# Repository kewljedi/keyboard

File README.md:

# keyboard

The purpose of this project is to make they keyboard that I want to use. It isn't a full keyboard instead it is a programable set of hot keys. 

Now of course the fact that I want these hot keys to be able to control things like tmux, vscode, and the like, doesn't make this keyboard nearly geeky enough, so it needs rgb leds, underglow, and a host of other cool things that the [Quantum Mechanical Keyboard Firmware](http://qmk.fm) affords those that use it.

This is a learning experience, the idea is to learn about electronics pcb design, and refresh my electronics knowledge. As a learning aid I started with [ruiqimao's keyboard pcb guide](https://github.com/ruiqimao/keyboard-pcb-guide).

## SIGHT

### underglow
To be able to pull of the awesome underglow effect we will be using the WS2812 RGB Addressable LED. I picked this because it is the same as the LEDs that are supported by the RBG Matrix. 

Parts
* [WS2812](https://www.sparkfun.com/products/16346)

### rgb matrix 
Of course each key needs an RGB Led of it's own. To accomplish this WS2812 comes to the rescue.

Parts
* [WS2812](https://www.sparkfun.com/products/16346)

### rotary encoders
A little bit of spin can go along way, if it is just to change the volume, or scrub through audio or video every good purpose built keyboard should have one rotary encoder at least, this keyboard will have RGB enabled ones. To do this the RGB Led inside the rotary encoder will be connected to a WS2811 Chip that will make the LED in the rotary encoder exactly like the NeoPixels used for the rest of the lighting. Don't forget the rotary encoder also contains a button.

Parts
* [Rotary Encoder](https://www.sparkfun.com/products/15141)
* [Clear Knob](https://www.sparkfun.com/products/10597)
* [LED Driver Chip WS2811](https://www.adafruit.com/product/1378)

## HEARING

### keys
[Gateron MX SMD Browns](https://www.amazon.com/Switches-Underglow-Compatible-Mechanical-Transparent/dp/B07K829KDW?th=1)

### speakers
Yes this board have two separate voices! It will play 8-bit tunes.

## FEELING

### keys
Cherry MX ... (still no color choice)

### keycaps 
I haven't decided but, I was thinking.

Parts 
* [Clear Keycaps](https://www.sparkfun.com/products/15306)

### haptic feedback
Now the feedback of the keys alone just wont cut it for this keyboard, it must be able to let us know when we have enters certain modes or functions.

Parts
* [DRV2605L](https://www.ti.com/product/DRV2605L?HQS=TI-null-null-digikeymode-df-pf-null-wwe&DCM=yes&distId=10)
* [Linear resonant actuators](https://www.digikey.com/product-detail/en/jinlong-machinery-electronics-inc/G0832013D/1670-1078-ND/9974290)

### case
So why stop learning wth just electronics and learning about the firmware? I think building the case will be just as much fun. I am thinking maybe wood, and epoxy resin (clear). One thing I want to keep in mind for the design of the case is wrist support.

### wires
No tug. Hopefully the only time you need to attach a USB-C cable to the keyboard is to charge it (though it should work wth one connected to you computer). This means that we have to have Bluetooth and Batteries.

Parts
* [Battery](https://www.sparkfun.com/products/12895)
* [Battery Holder](https://www.sparkfun.com/products/14963)
* [Battery Management]()
* [Bluetooth Module](https://www.adafruit.com/product/2633)

Insanity Parts
* [Wireless Power Receiver](https://www.sparkfun.com/products/15934)
* [Wireless Power Transmitter](https://www.sparkfun.com/products/15935)

## TASTE
By this point lets all agree ths keyboard sounds awesome enough to lick...

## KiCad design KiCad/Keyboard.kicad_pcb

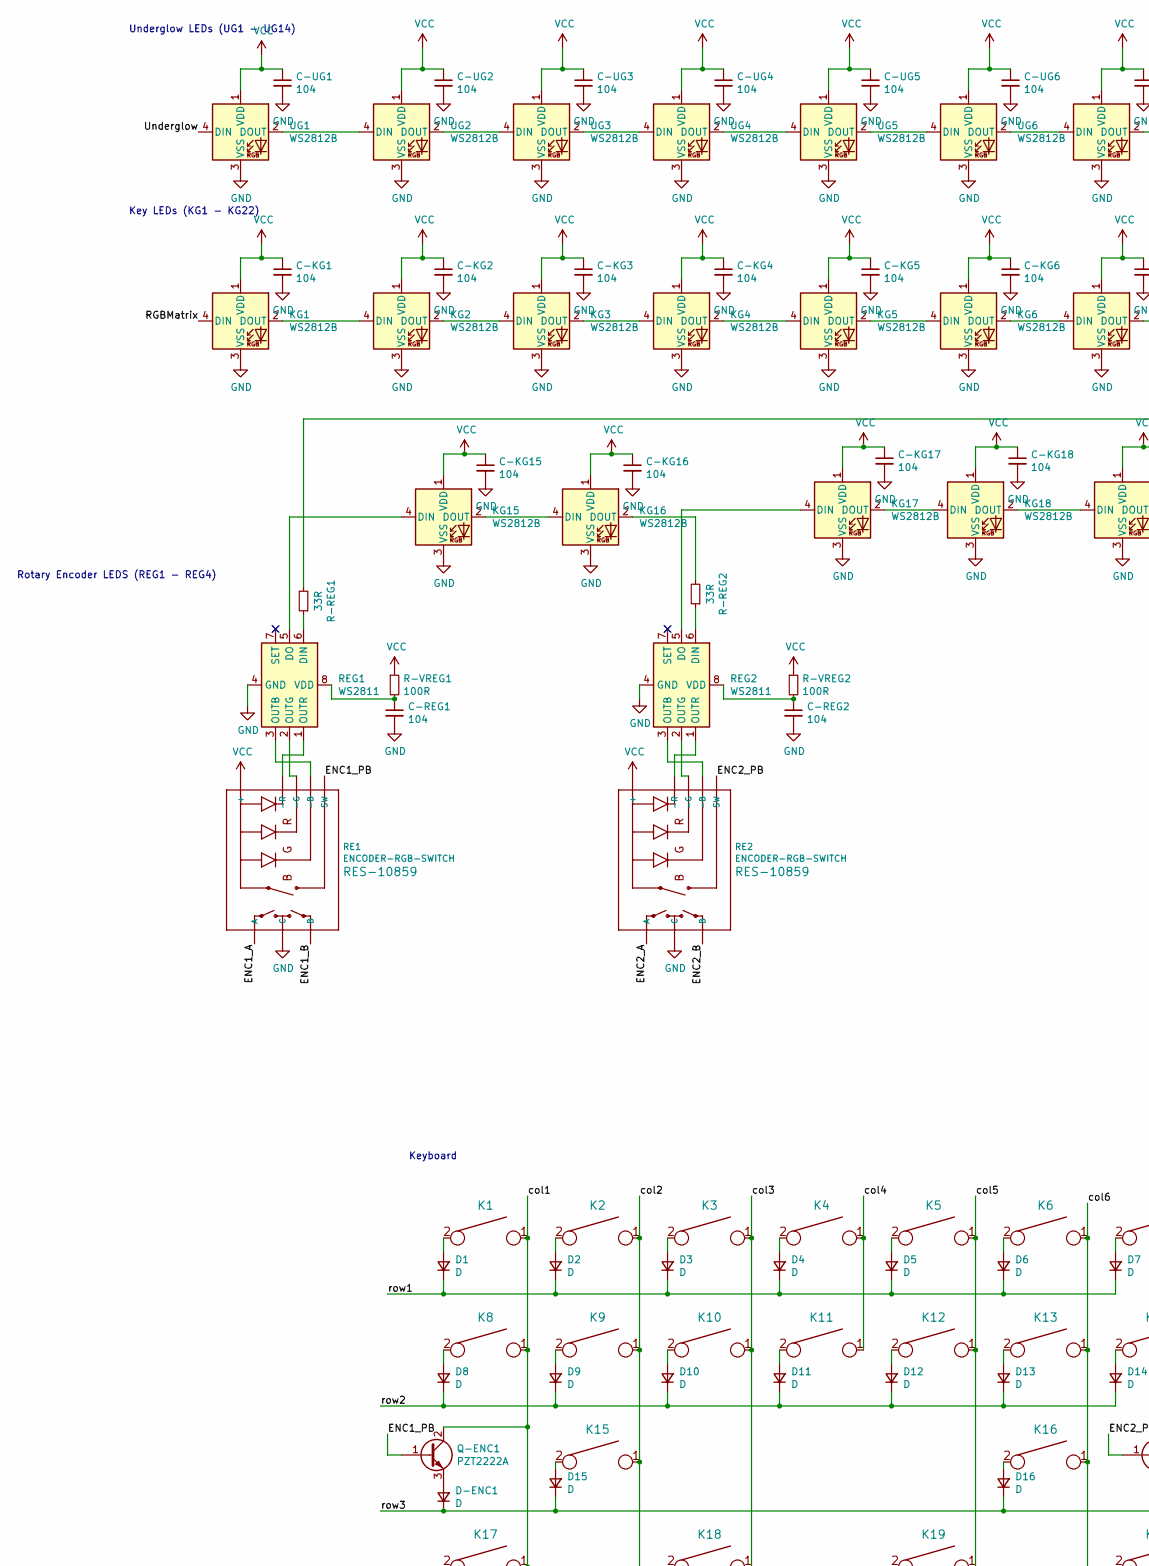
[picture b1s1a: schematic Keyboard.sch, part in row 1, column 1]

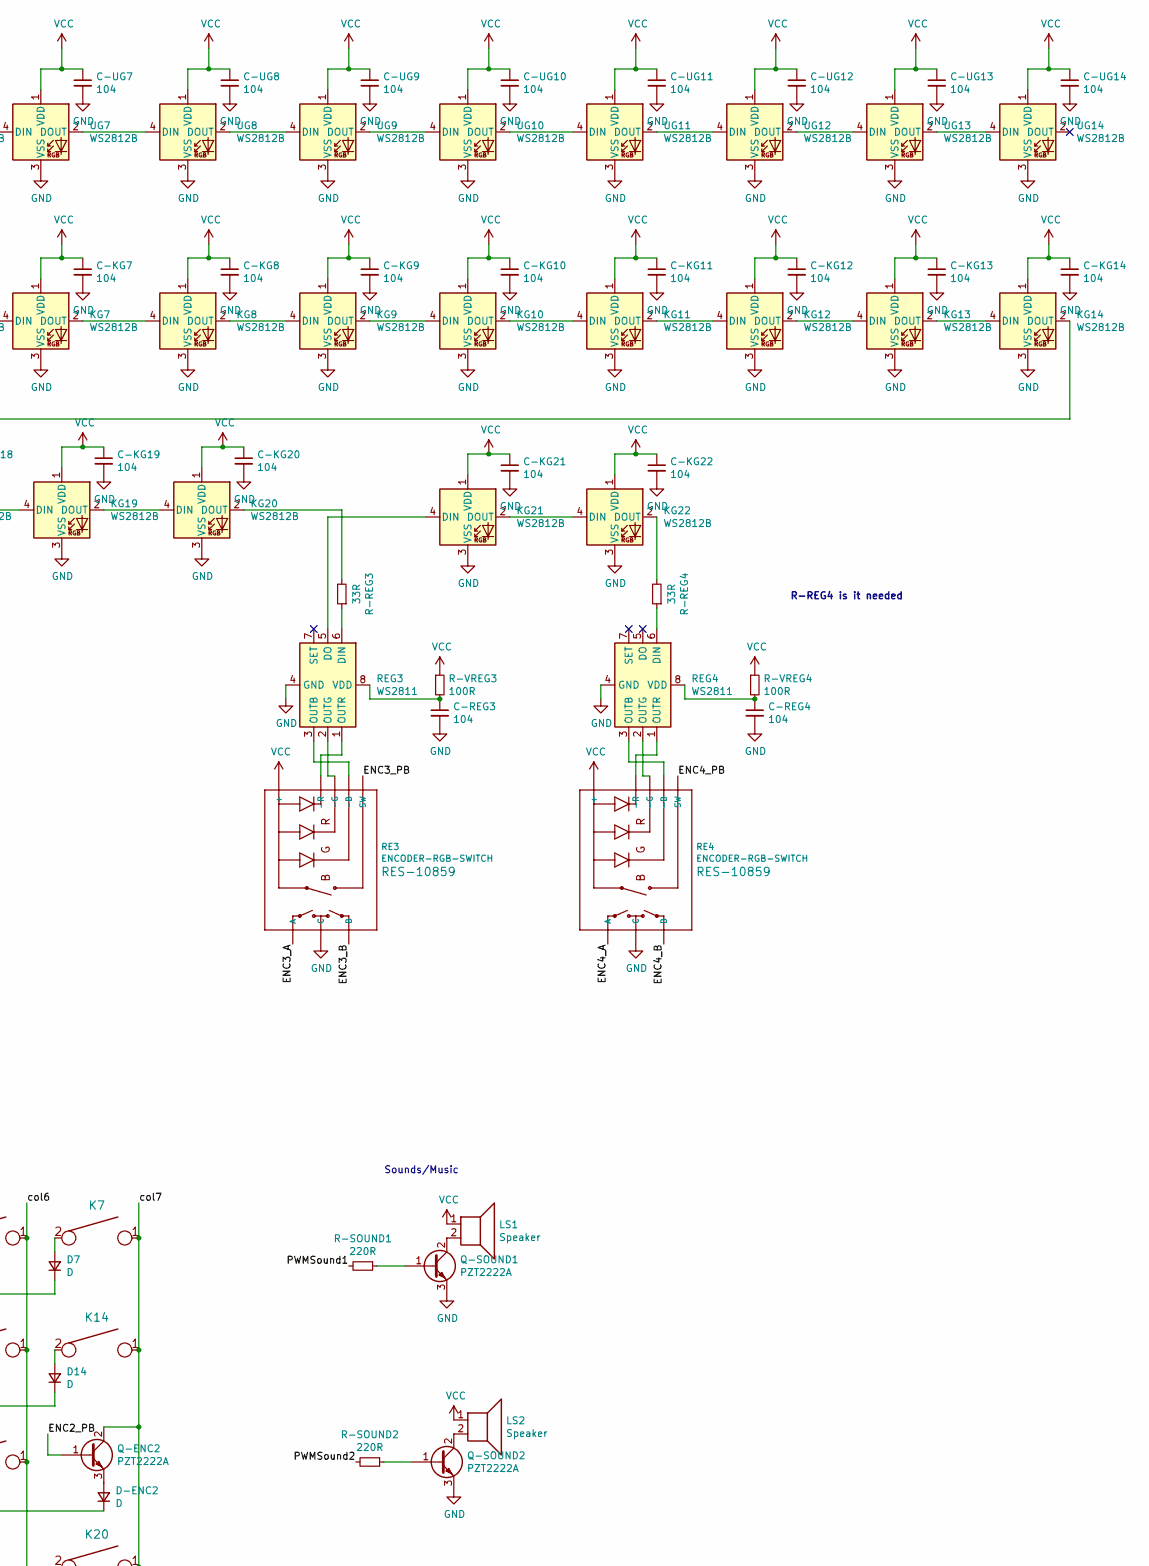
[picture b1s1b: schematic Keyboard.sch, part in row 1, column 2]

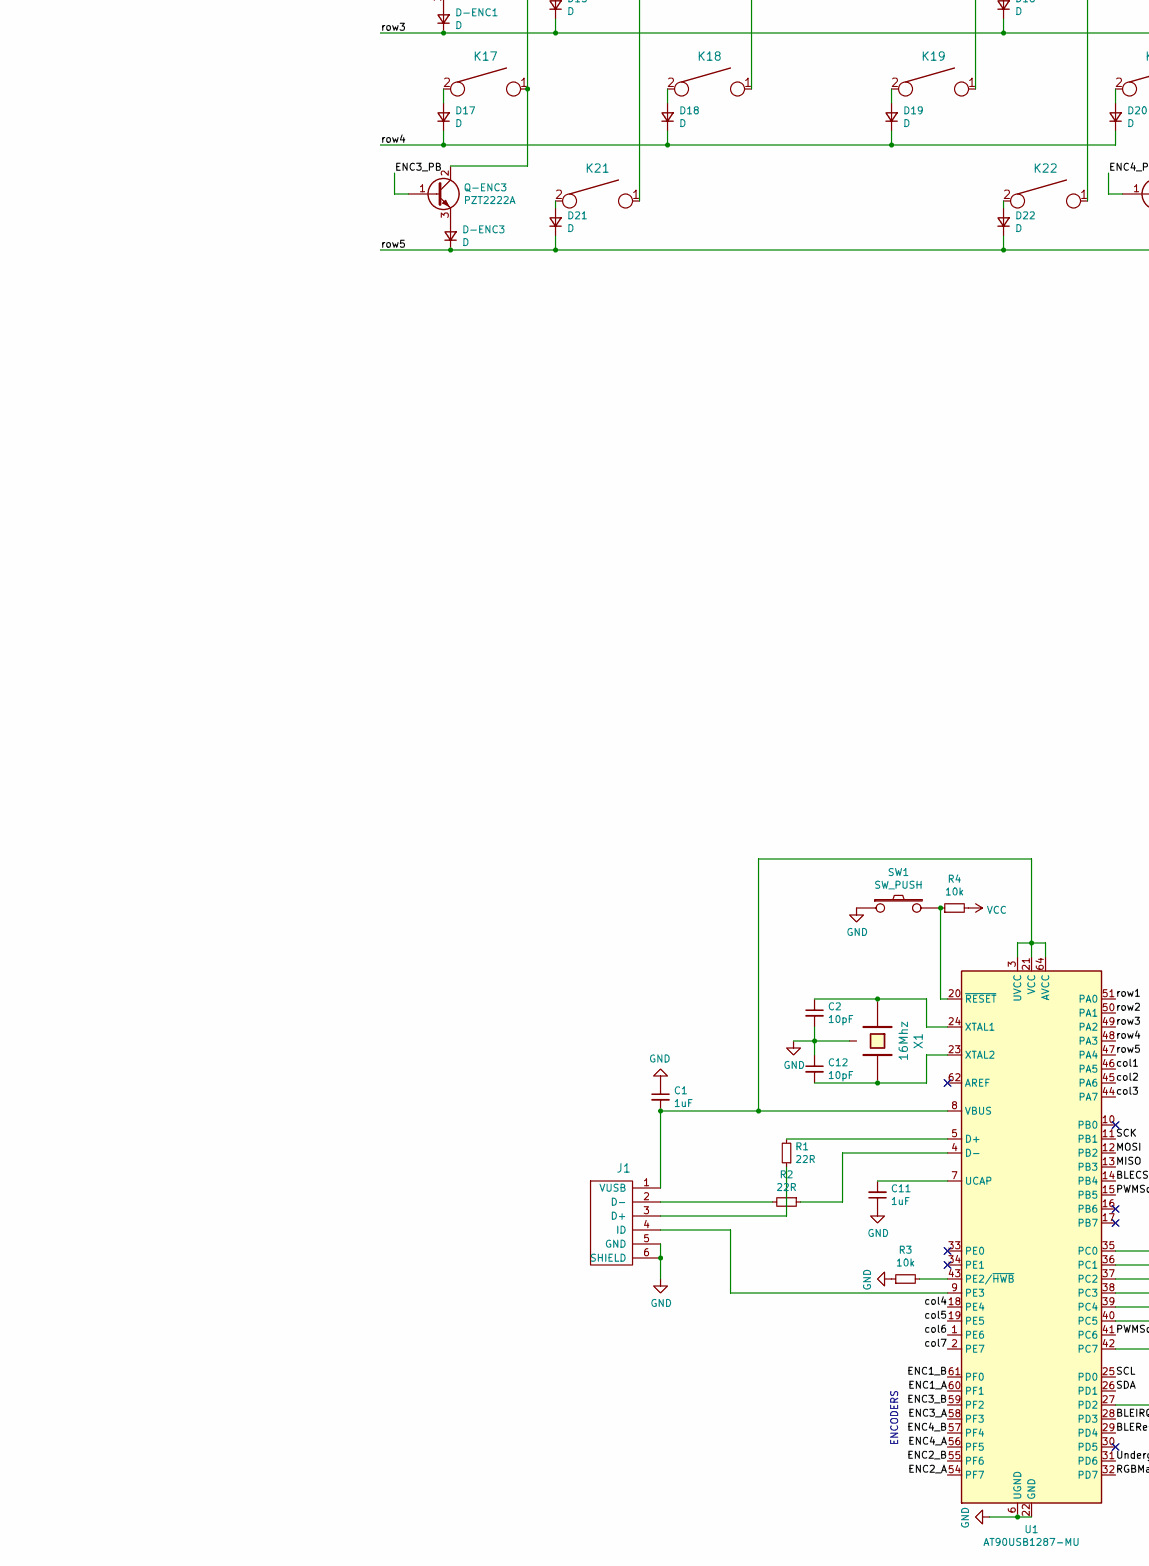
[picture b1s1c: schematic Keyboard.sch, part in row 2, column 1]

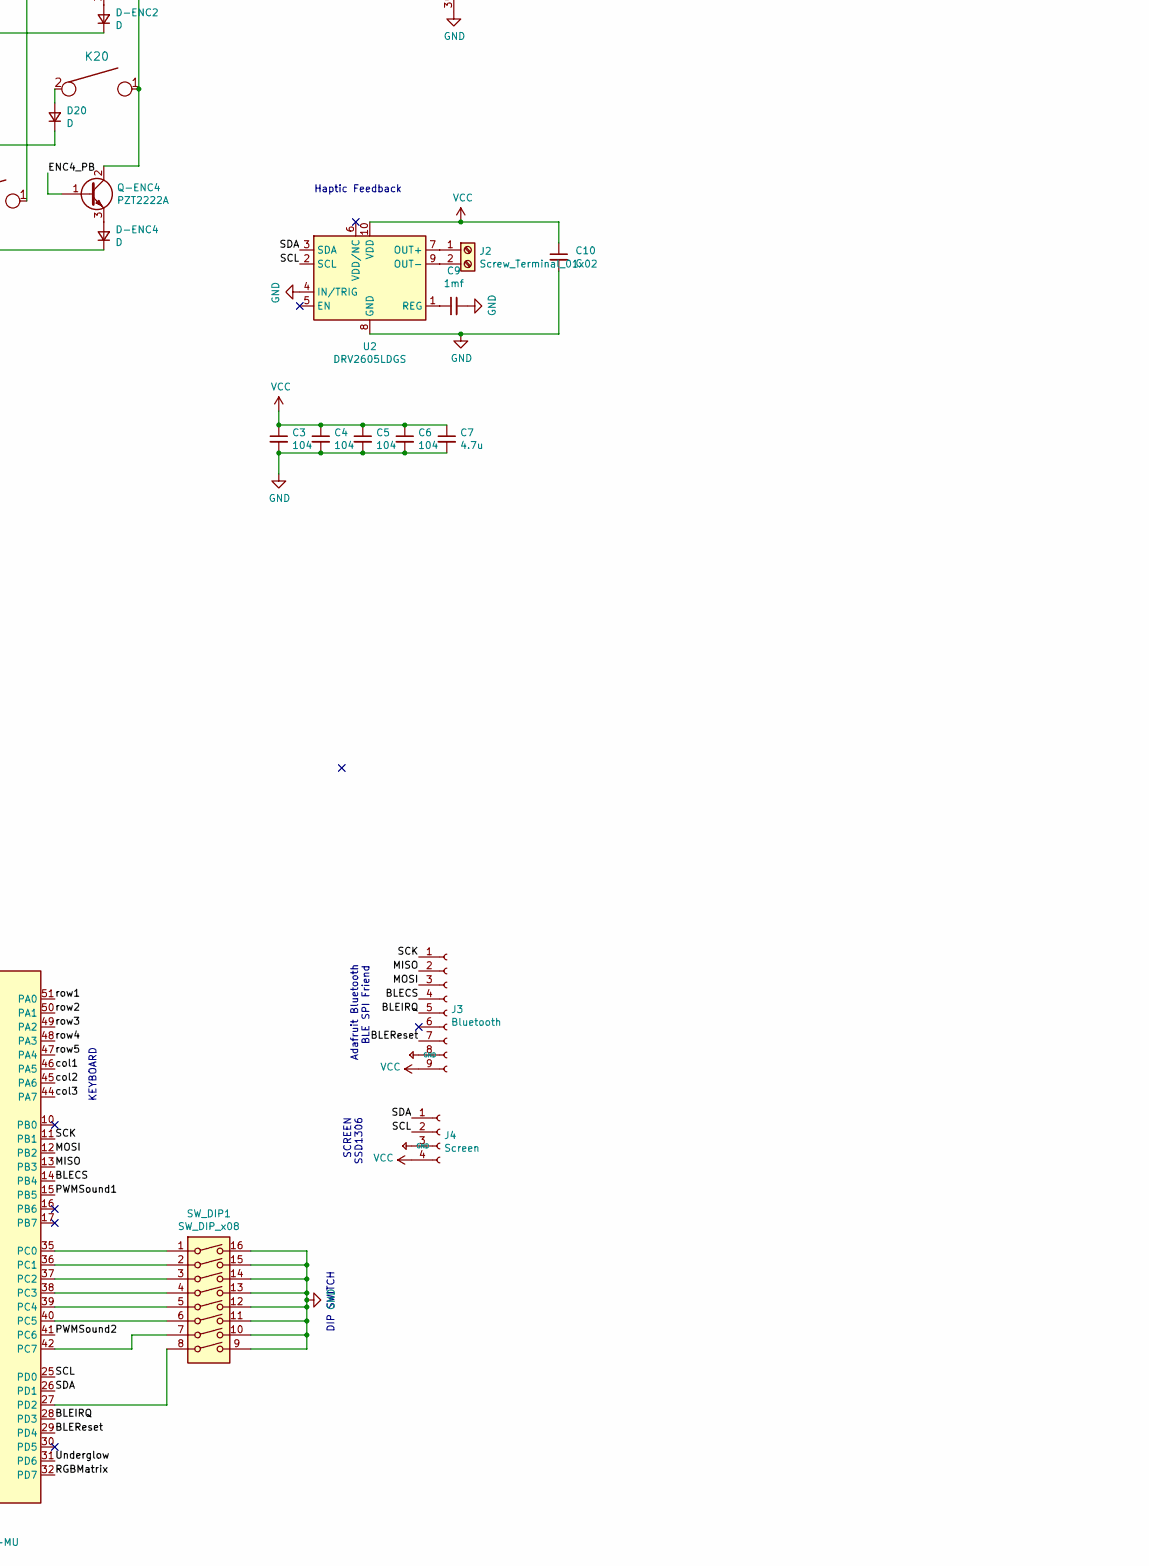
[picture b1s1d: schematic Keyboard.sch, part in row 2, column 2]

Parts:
C1, C11: 1uF; C_0201_0603Metric
C2, C12: 10pF; C_0201_0603Metric
C3, C4, C5, C6: 104; C_0201_0603Metric
C7: 4.7u; C_0201_0603Metric
C9: 1mf; C_0201_0603Metric
C10: C; C_0201_0603Metric
C-KG1, C-KG2, C-KG3, C-KG4, C-KG5, C-KG6, C-KG7, C-KG8, C-KG9, C-KG10, C-KG11, C-KG12, C-KG13, C-KG14, C-KG15, C-KG16, C-KG17, C-KG18, C-KG19, C-KG20, C-KG21, C-KG22: 104; C_0201_0603Metric
C-REG1, C-REG2, C-REG3, C-REG4: 104; C_0201_0603Metric
C-UG1, C-UG2, C-UG3, C-UG4, C-UG5, C-UG6, C-UG7, C-UG8, C-UG9, C-UG10, C-UG11, C-UG12, C-UG13: 104; C_0201_0603Metric
C-UG14: 104; D_0201_0603Metric
D1, D2, D3, D4, D5, D6, D7, D8, D9, D10, D11, D12, D13, D14, D15, D16, D17, D18, D19, D20, D21, D22: D; D_0201_0603Metric
D-ENC1, D-ENC2, D-ENC3, D-ENC4: D; D_0201_0603Metric
J1: USB_mini_micro_B; USB_Micro-B_Amphenol_10103594-0001LF_Horizontal
J2: Screw_Terminal_01x02; PinSocket_1x02_P1.00mm_Vertical_SMD_Pin1Left
J3: Bluetooth; PinSocket_1x04_P1.00mm_Vertical_SMD_Pin1Right
J4: Screen; PinSocket_1x03_P1.00mm_Vertical
K1, K2, K3, K4, K5, K6, K7, K8, K9, K10, K11, K12, K13, K14, K15, K16, K17, K18, K19, K20, K21, K22: KEYSW; SW_Cherry_MX_1.00u_Plate
KG1, KG2, KG3, KG4, KG5, KG6, KG7, KG8, KG9, KG10, KG11, KG12, KG13, KG14, KG15, KG16, KG17, KG18, KG19, KG20, KG21, KG22: WS2812B; LED_WS2812B_PLCC4_5.0x5.0mm_P3.2mm
LS1, LS2: Speaker; PinSocket_1x02_P1.00mm_Vertical_SMD_Pin1Left
Q-ENC1, Q-ENC2, Q-ENC3, Q-ENC4: PZT2222A; SOT-223-3_TabPin2
Q-SOUND1, Q-SOUND2: PZT2222A; SOT-223-3_TabPin2
R1, R2: 22R; R_0201_0603Metric
R3, R4: 10k; R_0201_0603Metric
R-REG1, R-REG2, R-REG3, R-REG4: 33R; R_0201_0603Metric
R-SOUND1, R-SOUND2: 220R; R_0201_0603Metric
R-VREG1, R-VREG2, R-VREG3, R-VREG4: 100R; R_0201_0603Metric
RE1, RE2, RE3, RE4: ENCODER-RGB-SWITCH; ENCODER_LED_3
REG1, REG2, REG3, REG4: WS2811; SOP-8_3.9x4.9mm_P1.27mm
SW1: SW_PUSH; SW_DIP_SPSTx01_Slide_6.7x4.1mm_W6.73mm_P2.54mm_LowProfile_J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
SW_DIP1: SW_DIP_x08; DIPSWITCH-08
U1: AT90USB1287-MU; QFN-64-1EP_9x9mm_P0.5mm_EP7.5x7.5mm
U2: DRV2605LDGS; VSSOP-10_3x3mm_P0.5mm
UG1, UG2, UG3, UG4, UG5, UG6, UG7, UG8, UG9, UG10, UG11, UG12, UG13, UG14: WS2812B; LED_WS2812B_PLCC4_5.0x5.0mm_P3.2mm
X1: 16Mhz; Crystal_SMD_0603-2Pin_6.0x3.5mm

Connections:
/BLECS: J3.4, U1.14 (PB4)
/BLEIRQ: J3.5, U1.28 (PD3)
/BLEReset: J3.7, U1.29 (PD4)
/ENC1_A: RE1.A, U1.60 (PF1)
/ENC1_B: RE1.B, U1.61 (PF0)
/ENC1_PB: Q-ENC1.1 (B), RE1.3 (SW)
/ENC2_A: RE2.A, U1.54 (PF7)
/ENC2_B: RE2.B, U1.55 (PF6)
/ENC2_PB: Q-ENC2.1 (B), RE2.3 (SW)
/ENC3_A: RE3.A, U1.58 (PF3)
/ENC3_B: RE3.B, U1.59 (PF2)
/ENC3_PB: Q-ENC3.1 (B), RE3.3 (SW)
/ENC4_A: RE4.A, U1.56 (PF5)
/ENC4_B: RE4.B, U1.57 (PF4)
/ENC4_PB: Q-ENC4.1 (B), RE4.3 (SW)
/MISO: J3.2, U1.13 (PB3)
/MOSI: J3.3, U1.12 (PB2)
/PWMSound1: R-SOUND1.2, U1.15 (PB5)
/PWMSound2: R-SOUND2.2, U1.41 (PC6)
/RGBMatrix: KG1.4 (DIN), U1.32 (PD7)
/SCK: J3.1, U1.11 (PB1)
/SCL: J4.2, U1.25 (PD0), U2.2 (SCL)
/SDA: J4.1, U1.26 (PD1), U2.3 (SDA)
/Underglow: U1.31 (PD6), UG1.4 (DIN)
/col1: K1.1, K8.1, K17.1, Q-ENC1.2 (C), Q-ENC3.2 (C), U1.46 (PA5)
/col2: K2.1, K9.1, K15.1, K21.1, U1.45 (PA6)
/col3: K3.1, K10.1, K18.1, U1.44 (PA7)
/col4: K4.1, K11.1, U1.18 (PE4)
/col5: K5.1, K12.1, K19.1, U1.19 (PE5)
/col6: K6.1, K13.1, K16.1, K22.1, U1.1 (PE6)
/col7: K7.1, K14.1, K20.1, Q-ENC2.2 (C), Q-ENC4.2 (C), U1.2 (PE7)
/row1: D1.1 (K), D2.1 (K), D3.1 (K), D4.1 (K), D5.1 (K), D6.1 (K), D7.1 (K), U1.51 (PA0)
/row2: D8.1 (K), D9.1 (K), D10.1 (K), D11.1 (K), D12.1 (K), D13.1 (K), D14.1 (K), U1.50 (PA1)
/row3: D15.1 (K), D16.1 (K), D-ENC1.1 (K), D-ENC2.1 (K), U1.49 (PA2)
/row4: D17.1 (K), D18.1 (K), D19.1 (K), D20.1 (K), U1.48 (PA3)
/row5: D21.1 (K), D22.1 (K), D-ENC3.1 (K), D-ENC4.1 (K), U1.47 (PA4)
unnamed: C1.2, J1.1 (VUSB), U1.3 (UVCC), U1.8 (VBUS), U1.21 (VCC), U1.52 (VCC), U1.64 (AVCC)
unnamed: C2.1, U1.24 (XTAL1), X1.1
unnamed: C9.1, U2.1 (REG)
unnamed: C11.2, U1.7 (UCAP)
unnamed: C12.2, U1.23 (XTAL2), X1.2
unnamed: C-REG1.1, R-VREG1.2, REG1.8 (VDD)
unnamed: C-REG2.1, R-VREG2.2, REG2.8 (VDD)
unnamed: C-REG3.1, R-VREG3.2, REG3.8 (VDD)
unnamed: C-REG4.1, R-VREG4.2, REG4.8 (VDD)
unnamed: D1.2 (A), K1.2
unnamed: D2.2 (A), K2.2
unnamed: D3.2 (A), K3.2
unnamed: D4.2 (A), K4.2
unnamed: D5.2 (A), K5.2
unnamed: D6.2 (A), K6.2
unnamed: D7.2 (A), K7.2
unnamed: D8.2 (A), K8.2
unnamed: D9.2 (A), K9.2
unnamed: D10.2 (A), K10.2
unnamed: D11.2 (A), K11.2
unnamed: D12.2 (A), K12.2
unnamed: D13.2 (A), K13.2
unnamed: D14.2 (A), K14.2
unnamed: D15.2 (A), K15.2
unnamed: D16.2 (A), K16.2
unnamed: D17.2 (A), K17.2
unnamed: D18.2 (A), K18.2
unnamed: D19.2 (A), K19.2
unnamed: D20.2 (A), K20.2
unnamed: D21.2 (A), K21.2
unnamed: D22.2 (A), K22.2
unnamed: D-ENC1.2 (A), Q-ENC1.3 (E)
unnamed: D-ENC2.2 (A), Q-ENC2.3 (E)
unnamed: D-ENC3.2 (A), Q-ENC3.3 (E)
unnamed: D-ENC4.2 (A), Q-ENC4.3 (E)
unnamed: J1.2 (D-), R2.2
unnamed: J1.3 (D+), R1.1
unnamed: J1.4 (ID), U1.9 (PE3)
unnamed: J2.1, U2.7 (OUT+)
unnamed: J2.2, U2.9 (OUT-)
unnamed: KG1.2 (DOUT), KG2.4 (DIN)
unnamed: KG2.2 (DOUT), KG3.4 (DIN)
unnamed: KG3.2 (DOUT), KG4.4 (DIN)
unnamed: KG4.2 (DOUT), KG5.4 (DIN)
unnamed: KG5.2 (DOUT), KG6.4 (DIN)
unnamed: KG6.2 (DOUT), KG7.4 (DIN)
unnamed: KG7.2 (DOUT), KG8.4 (DIN)
unnamed: KG8.2 (DOUT), KG9.4 (DIN)
unnamed: KG10.2 (DOUT), KG11.4 (DIN)
unnamed: KG9.2 (DOUT), KG10.4 (DIN)
unnamed: KG11.2 (DOUT), KG12.4 (DIN)
unnamed: KG12.2 (DOUT), KG13.4 (DIN)
unnamed: KG13.2 (DOUT), KG14.4 (DIN)
unnamed: KG14.2 (DOUT), R-REG1.2
unnamed: KG15.2 (DOUT), KG16.4 (DIN)
unnamed: KG15.4 (DIN), REG1.5 (DO)
unnamed: KG16.2 (DOUT), R-REG2.2
unnamed: KG17.2 (DOUT), KG18.4 (DIN)
unnamed: KG17.4 (DIN), REG2.5 (DO)
unnamed: KG18.2 (DOUT), KG19.4 (DIN)
unnamed: KG19.2 (DOUT), KG20.4 (DIN)
unnamed: KG20.2 (DOUT), R-REG3.2
unnamed: KG21.2 (DOUT), KG22.4 (DIN)
unnamed: KG21.4 (DIN), REG3.5 (DO)
unnamed: KG22.2 (DOUT), R-REG4.2
unnamed: LS1.2, Q-SOUND1.2 (C)
unnamed: LS2.2, Q-SOUND2.2 (C)
unnamed: Q-SOUND1.1 (B), R-SOUND1.1
unnamed: Q-SOUND2.1 (B), R-SOUND2.1
unnamed: R1.2, U1.5 (D+)
unnamed: R2.1, U1.4 (D-)
unnamed: R3.2, U1.43 (PE2/~HWB)
unnamed: R4.1, SW1.2, U1.20 (~RESET)
unnamed: R-REG1.1, REG1.6 (DIN)
unnamed: R-REG2.1, REG2.6 (DIN)
unnamed: R-REG3.1, REG3.6 (DIN)
unnamed: R-REG4.1, REG4.6 (DIN)
unnamed: RE1.1 (-R), REG1.1 (OUTR)
unnamed: RE1.2 (-G), REG1.2 (OUTG)
unnamed: RE1.4 (-B), REG1.3 (OUTB)
unnamed: RE2.1 (-R), REG2.1 (OUTR)
unnamed: RE2.2 (-G), REG2.2 (OUTG)
unnamed: RE2.4 (-B), REG2.3 (OUTB)
unnamed: RE3.1 (-R), REG3.1 (OUTR)
unnamed: RE3.2 (-G), REG3.2 (OUTG)
unnamed: RE3.4 (-B), REG3.3 (OUTB)
unnamed: RE4.1 (-R), REG4.1 (OUTR)
unnamed: RE4.2 (-G), REG4.2 (OUTG)
unnamed: RE4.4 (-B), REG4.3 (OUTB)
unnamed: SW_DIP1.1, U1.35 (PC0)
unnamed: SW_DIP1.2, U1.36 (PC1)
unnamed: SW_DIP1.3, U1.37 (PC2)
unnamed: SW_DIP1.4, U1.38 (PC3)
unnamed: SW_DIP1.5, U1.39 (PC4)
unnamed: SW_DIP1.6, U1.40 (PC5)
unnamed: SW_DIP1.7, U1.42 (PC7)
unnamed: SW_DIP1.8, U1.27 (PD2)
unnamed: UG1.2 (DOUT), UG2.4 (DIN)
unnamed: UG2.2 (DOUT), UG3.4 (DIN)
unnamed: UG3.2 (DOUT), UG4.4 (DIN)
unnamed: UG4.2 (DOUT), UG5.4 (DIN)
unnamed: UG5.2 (DOUT), UG6.4 (DIN)
unnamed: UG6.2 (DOUT), UG7.4 (DIN)
unnamed: UG7.2 (DOUT), UG8.4 (DIN)
unnamed: UG8.2 (DOUT), UG9.4 (DIN)
unnamed: UG10.2 (DOUT), UG11.4 (DIN)
unnamed: UG9.2 (DOUT), UG10.4 (DIN)
unnamed: UG11.2 (DOUT), UG12.4 (DIN)
unnamed: UG12.2 (DOUT), UG13.4 (DIN)
unnamed: UG13.2 (DOUT), UG14.4 (DIN)
VCC: C3.1, C4.1, C5.1, C6.1, C7.1, C10.1, C-KG1.1, C-KG2.1, C-KG3.1, C-KG4.1, C-KG5.1, C-KG6.1, C-KG7.1, C-KG8.1, C-KG9.1, C-KG10.1, C-KG11.1, C-KG12.1, C-KG13.1, C-KG14.1, C-KG15.1, C-KG16.1, C-KG17.1, C-KG18.1, C-KG19.1, C-KG20.1, C-KG21.1, C-KG22.1, C-UG1.1, C-UG2.1, C-UG3.1, C-UG4.1, C-UG5.1, C-UG6.1, C-UG7.1, C-UG8.1, C-UG9.1, C-UG10.1, C-UG11.1, C-UG12.1, C-UG13.1, C-UG14.1, J3.9, J4.4, KG1.1 (VDD), KG2.1 (VDD), KG3.1 (VDD), KG4.1 (VDD), KG5.1 (VDD), KG6.1 (VDD), KG7.1 (VDD), KG8.1 (VDD), KG9.1 (VDD), KG10.1 (VDD), KG11.1 (VDD), KG12.1 (VDD), KG13.1 (VDD), KG14.1 (VDD), KG15.1 (VDD), KG16.1 (VDD), KG17.1 (VDD), KG18.1 (VDD), KG19.1 (VDD), KG20.1 (VDD), KG21.1 (VDD), KG22.1 (VDD), LS1.1, LS2.1, R4.2, R-VREG1.1, R-VREG2.1, R-VREG3.1, R-VREG4.1, RE1.5 (+), RE2.5 (+), RE3.5 (+), RE4.5 (+), U2.10 (VDD), UG1.1 (VDD), UG2.1 (VDD), UG3.1 (VDD), UG4.1 (VDD), UG5.1 (VDD), UG6.1 (VDD), UG7.1 (VDD), UG8.1 (VDD), UG9.1 (VDD), UG10.1 (VDD), UG11.1 (VDD), UG12.1 (VDD), UG13.1 (VDD), UG14.1 (VDD)

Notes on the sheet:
Key LEDs (KG1 - KG22)
Rotary Encoder LEDS (REG1 - REG4)
R-REG4 is it needed
Keyboard
ENCODERS
KEYBOARD
Haptic Feedback
Sounds/Music
Underglow LEDs (UG1 - UG14)
DIP SWITCH
Adafruit Bluetooth BLE SPI Friend
SCREEN SSD1306

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
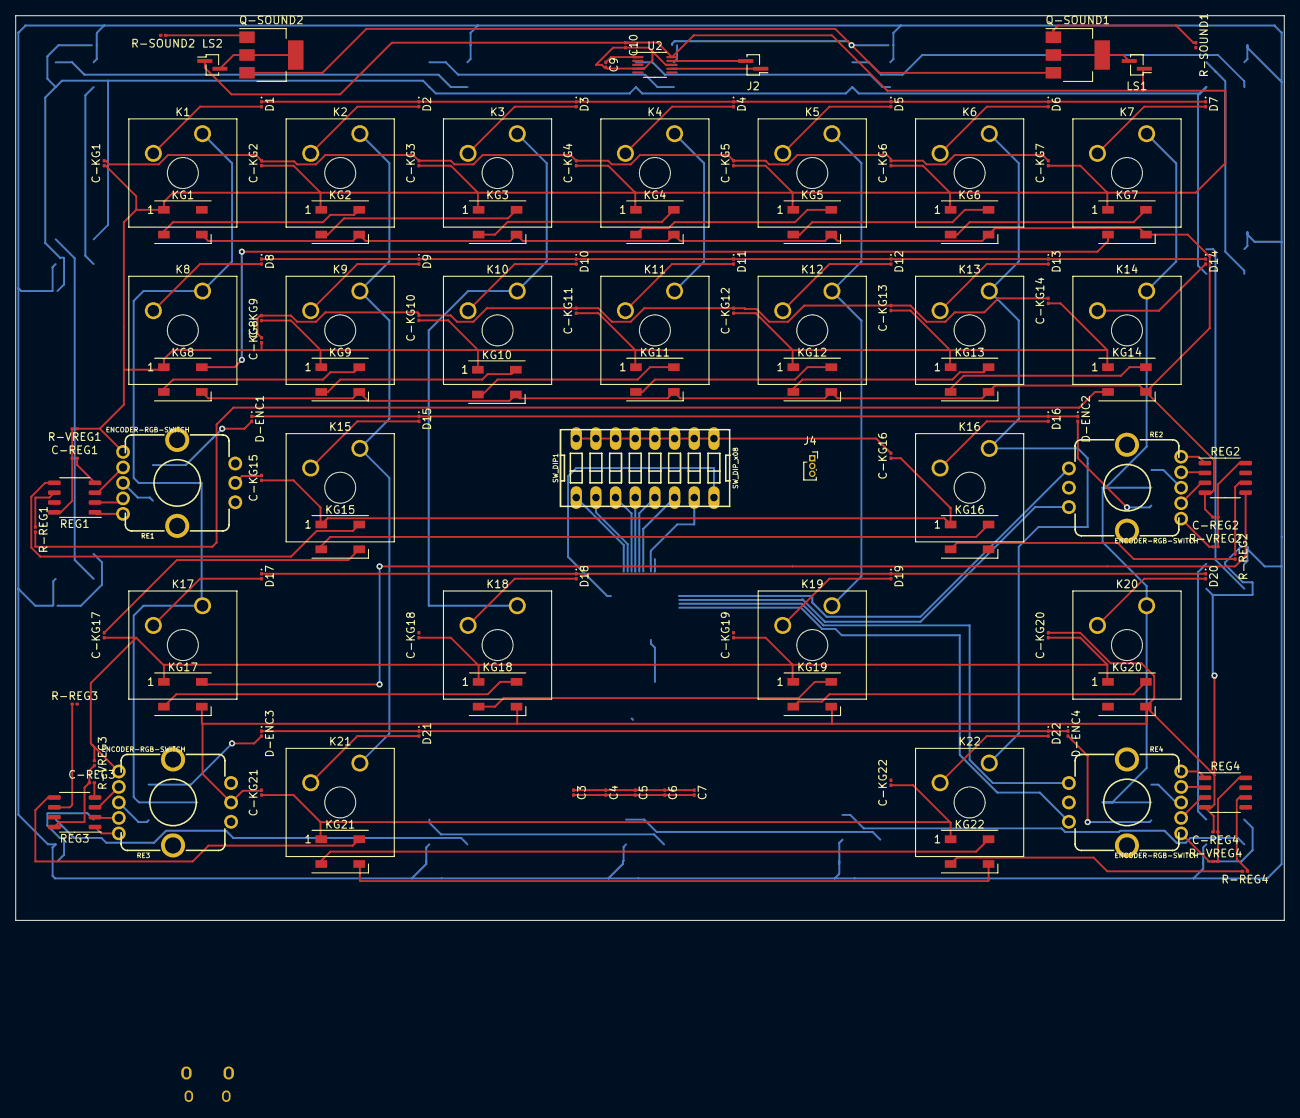
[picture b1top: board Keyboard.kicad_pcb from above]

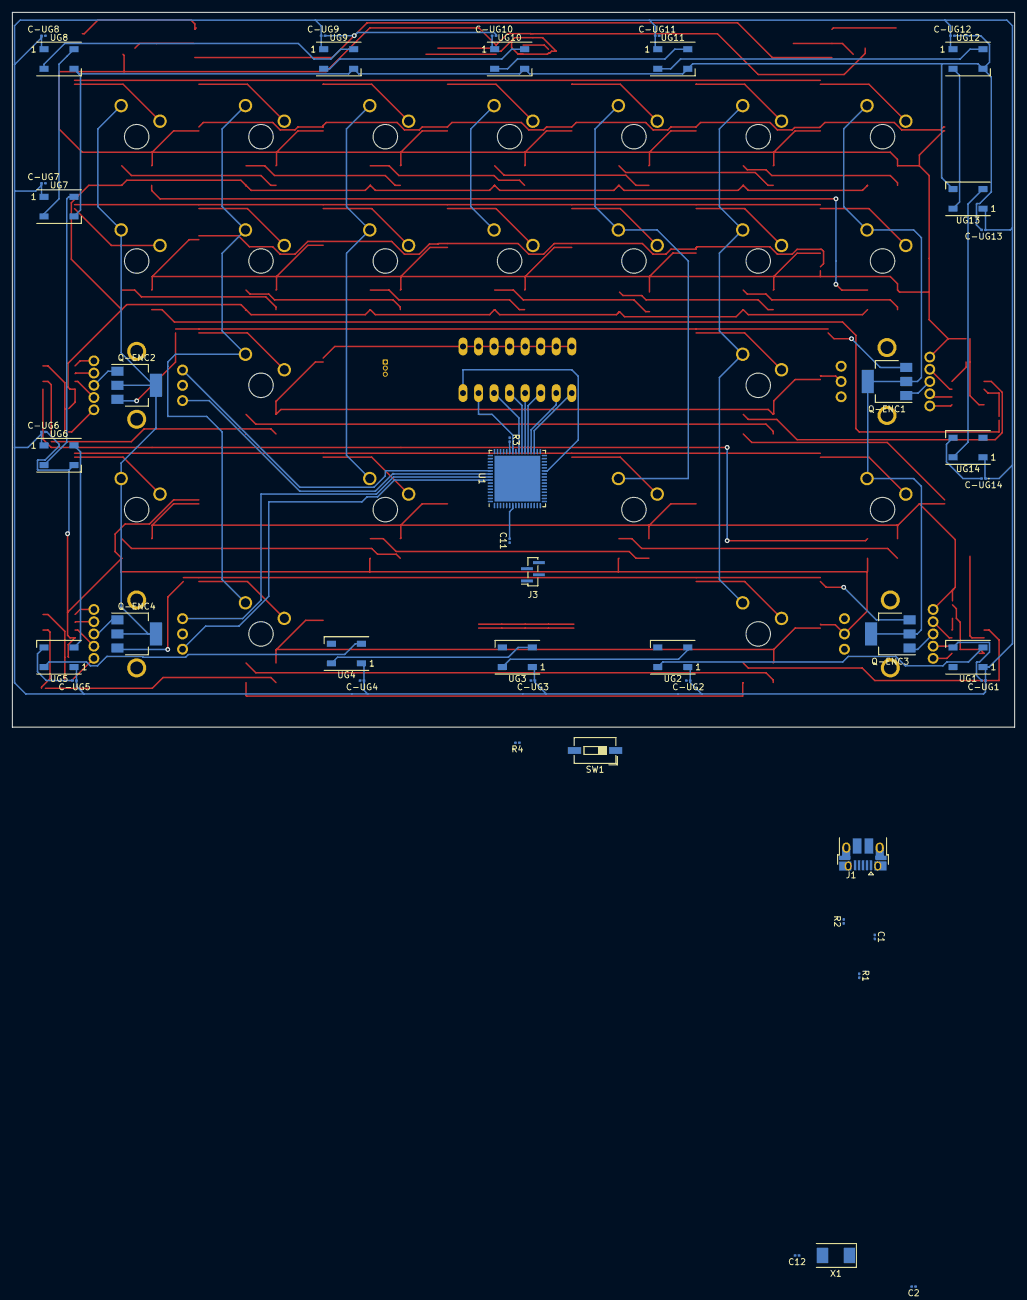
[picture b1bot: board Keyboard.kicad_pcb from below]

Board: 2 copper layers, 163.8 x 116.8 mm, 174 parts (45 on the bottom side), 146 nets.

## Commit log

2020-05-24 Initial commit, just starting to learn please don't judge to harshly.
2020-05-24 Completed COl connectons an UG and KG LEDS started RE LED connections
2020-05-24 A bit closer, ran out of pins on MCU ugh!!
2020-05-25 all LEDs I think are setup, one question there in bold.
2020-05-26 Changed to SMALL components
2020-05-26 small changes
2020-05-28 Got the envoder switches wired up
2020-05-29 well out of pins.. no bluetooh yet
2020-06-03 lots of changes, and trying to get qmk done
2020-12-27 lots of changes
